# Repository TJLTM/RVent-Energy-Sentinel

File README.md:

# RVent-Energy-Sentinel

Need a custom thing to monitor the low voltage stuff in an RV. This is to make sure I don't Rip & Tear through stored energy 

Current requirements 
1. Monitor the voltage on 3-4 Banks of batteries 
2. monitor the temp of each bank 
3. able to connect/disconnect banks from load 
4. able to connect/disconnect banks from charger
5. RS232 Communications and control 
6. Voltage Level on each Bank 
7. Current Draw from each bank. 
8. Inverter control

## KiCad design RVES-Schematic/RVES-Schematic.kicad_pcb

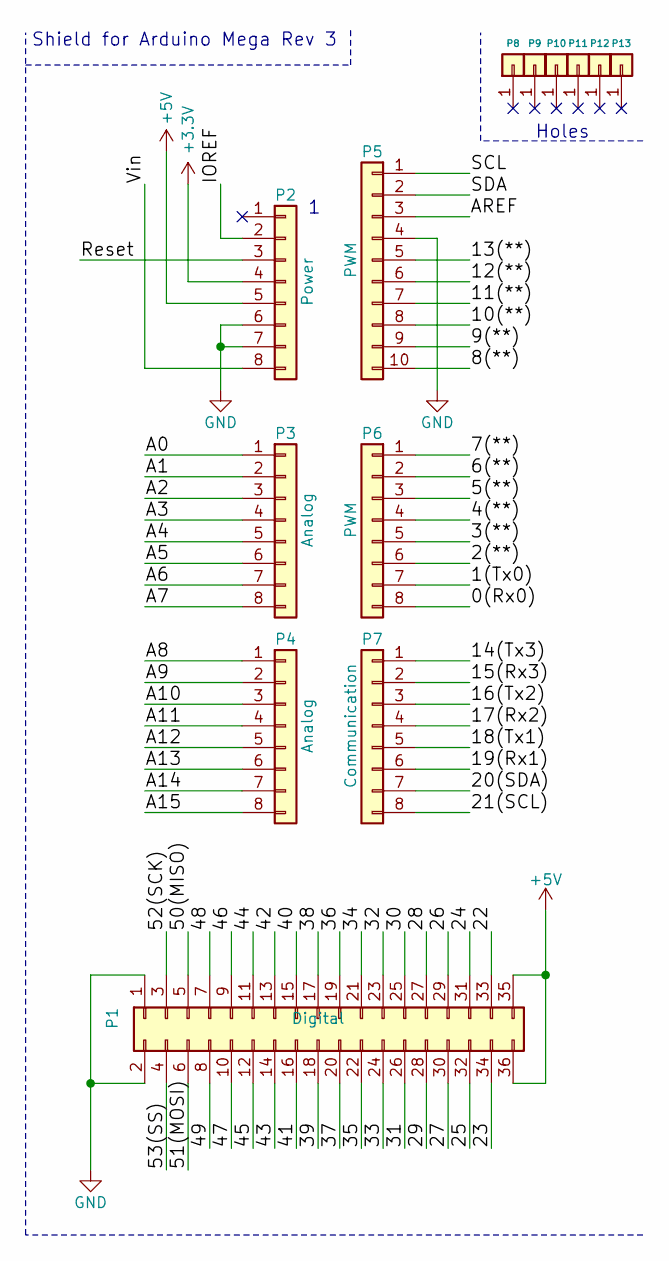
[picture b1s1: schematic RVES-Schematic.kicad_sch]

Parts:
P1: Digital; Socket_Strip_Arduino_2x18
P2: Power; Socket_Strip_Arduino_1x08
P3, P4: Analog; Socket_Strip_Arduino_1x08
P5: PWM; Socket_Strip_Arduino_1x10
P6: PWM; Socket_Strip_Arduino_1x08
P7: Communication; Socket_Strip_Arduino_1x08
P8, P9, P10, P11, P12, P13: CONN_01X01; Arduino_1pin

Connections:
+3V3: P2.4
+5V: P1.35, P1.36, P2.5
/0(Rx0): P6.8
/1(Tx0): P6.7
/2(**): P6.6
/3(**): P6.5
/4(**): P6.4
/5(**): P6.3
/6(**): P6.2
/7(**): P6.1
/8(**): P5.10
/9(**): P5.9
/10(**): P5.8
/11(**): P5.7
/12(**): P5.6
/13(**): P5.5
/14(Tx3): P7.1
/15(Rx3): P7.2
/16(Tx2): P7.3
/17(Rx2): P7.4
/18(Tx1): P7.5
/19(Rx1): P7.6
/20(SDA): P7.7
/21(SCL): P7.8
/22: P1.33
/23: P1.34
/24: P1.31
/25: P1.32
/26: P1.29
/27: P1.30
/28: P1.27
/29: P1.28
/30: P1.25
/31: P1.26
/32: P1.23
/33: P1.24
/34: P1.21
/35: P1.22
/36: P1.19
/37: P1.20
/38: P1.17
/39: P1.18
/40: P1.15
/41: P1.16
/42: P1.13
/43: P1.14
/44: P1.11
/45: P1.12
/46: P1.9
/47: P1.10
/48: P1.7
/49: P1.8
/50(MISO): P1.5
/51(MOSI): P1.6
/52(SCK): P1.3
/53(SS): P1.4
/A0: P3.1
/A1: P3.2
/A2: P3.3
/A3: P3.4
/A4: P3.5
/A5: P3.6
/A6: P3.7
/A7: P3.8
/A8: P4.1
/A9: P4.2
/A10: P4.3
/A11: P4.4
/A12: P4.5
/A13: P4.6
/A14: P4.7
/A15: P4.8
/AREF: P5.3
/IOREF: P2.2
/Reset: P2.3
/SCL: P5.1
/SDA: P5.2
/Vin: P2.8
GND: P1.1, P1.2, P2.6, P2.7, P5.4

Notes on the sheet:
Holes
Shield for Arduino Mega Rev 3

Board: 2 copper layers, 13 parts (0 on the bottom side), 2 nets, no tracks yet.

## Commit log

2022-06-03 initial kicad project
